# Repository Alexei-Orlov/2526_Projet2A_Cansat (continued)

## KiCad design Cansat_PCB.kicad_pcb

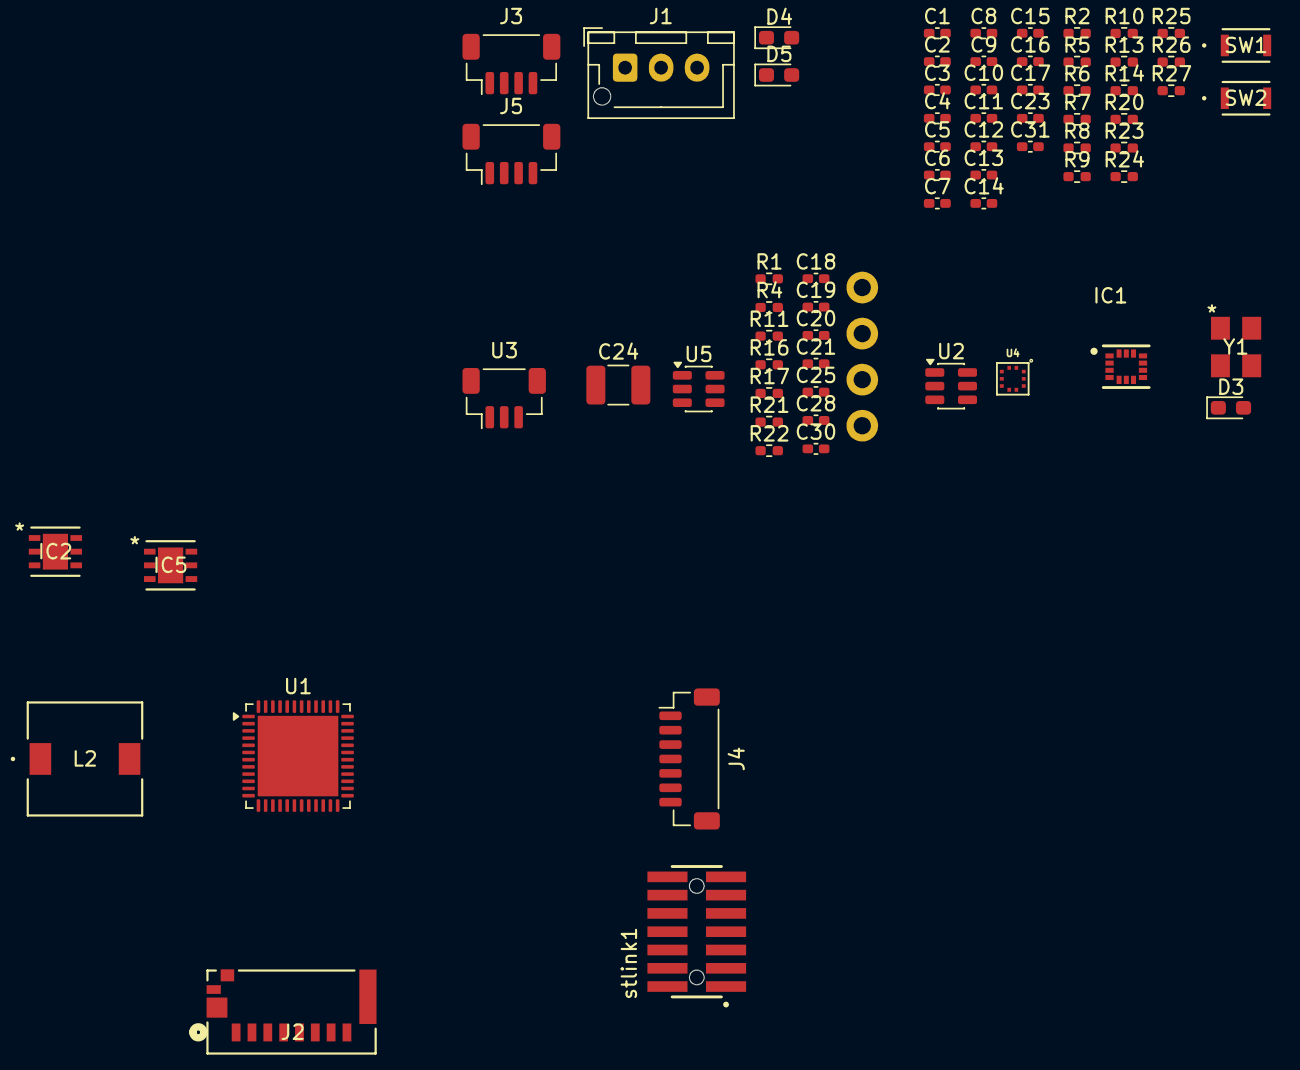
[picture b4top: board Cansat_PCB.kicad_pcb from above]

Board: 2 copper layers, 74 parts (0 on the bottom side), 50 nets, no tracks yet.

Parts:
C1, C4, C5, C6, C9, C16, C23, C30, C31: 100n; C_0402_1005Metric_Pad0.74x0.62mm_HandSolder
C2: 0.1u; C_0402_1005Metric_Pad0.74x0.62mm_HandSolder
C3, C7, C14: 10n; C_0402_1005Metric_Pad0.74x0.62mm_HandSolder
C8, C10, C18, C19, C20, C21: 1u; C_0402_1005Metric_Pad0.74x0.62mm_HandSolder
C11, C15: 4.7u; C_0402_1005Metric_Pad0.74x0.62mm_HandSolder
C12, C13: 16p; C_0402_1005Metric_Pad0.74x0.62mm_HandSolder
C17: 10u; C_0402_1005Metric_Pad0.74x0.62mm_HandSolder
C24: 0.1u; C_1210_3225Metric_Pad1.33x2.70mm_HandSolder
C25: 2.2u; C_0402_1005Metric_Pad0.74x0.62mm_HandSolder
C28: 66u; C_0402_1005Metric_Pad0.74x0.62mm_HandSolder
D3, D4, D5: LED; LED_0603_1608Metric_Pad1.05x0.95mm_HandSolder
H1, H2, H3, H4: MountingHole_Pad; mountinghole1.2mm
IC1: 2536030320001; WSEN-ISDS_2536030320001
IC2, IC5: LDO40LPU33RY; DFN6_3X3_STM
J1: battery connector; JST_XH_B3B-XH-AM_1x03_P2.50mm_Vertical
J2: 47309-2651; CONN12_47309-2651_MOL
J3: connecteur gps; JST_SH_BM04B-SRSS-TB_1x04-1MP_P1.00mm_Vertical
J4: Conn_01x07_Pin; JST_SH_BM07B-SRSS-TB_1x07-1MP_P1.00mm_Vertical
J5: Conn_01x04_Pin; JST_SH_BM04B-SRSS-TB_1x04-1MP_P1.00mm_Vertical
L2: 10u; IND_WE-PD-SMT_7332_WRE
R1: 100k; R_0402_1005Metric_Pad0.72x0.64mm_HandSolder
R2, R5, R6, R22, R23, R25: 10k; R_0402_1005Metric_Pad0.72x0.64mm_HandSolder
R4, R11: 1k; R_0402_1005Metric_Pad0.72x0.64mm_HandSolder
R7, R8, R9, R10: 47k; R_0402_1005Metric_Pad0.72x0.64mm_HandSolder
R13, R14: 10R; R_0402_1005Metric_Pad0.72x0.64mm_HandSolder
R16: 53.6k; R_0402_1005Metric_Pad0.72x0.64mm_HandSolder
R17: 10.2k; R_0402_1005Metric_Pad0.72x0.64mm_HandSolder
R20: 1.1k; R_0402_1005Metric_Pad0.72x0.64mm_HandSolder
R21: 20k; R_0402_1005Metric_Pad0.72x0.64mm_HandSolder
R24: 0R; R_0402_1005Metric_Pad0.72x0.64mm_HandSolder
R26, R27: 2.2k; R_0402_1005Metric_Pad0.72x0.64mm_HandSolder
SW1: RSTBTN; KXT 321 LHS_CNK
SW2: boot; KXT 321 LHS_CNK
U1: STM32G431CBUx; QFN-48-1EP_7x7mm_P0.5mm_EP5.6x5.6mm
U2: USBLC6-2SC6; SOT-23-6
U3: Connecteur moteur; JST_SH_BM03B-SRSS-TB_1x03-1MP_P1.00mm_Vertical
U4: BMP581
U5: LMR51625; SOT-23-6
Y1: Crystal_GND24_Small; SMD3225_3.2X2.5X0.7_MTC
stlink1: FTSH-107-01-L-DV-K-A; SAMTEC_FTSH-107-01-L-DV-K-A

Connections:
3.3VEN: C20.1, C21.1, D4.2 (A), D5.2 (A), IC2.4 (VOUT), IC2.5 (VSENSE), IC5.4 (VOUT), IC5.5 (VSENSE), J3.1
+3.3V: C1.1, C4.2, C5.2, C6.2, C7.2, C8.2, C9.2, C10.2, C11.1, C15.1, C16.1, C17.1, IC1.2 (RSVD_1), IC1.3 (RSVD_2), IC1.5 (VDD_IO), IC1.8 (VDD), IC1.11 (RSVD_4), IC1.12 (CS), J2.4, J4.2, R5.1, R7.2, R8.1, R9.1, R10.2, R13.1, R14.1, R23.1, R25.2, R26.2, R27.1, SW2.2, U1.1 (VBAT), U1.20 (VREF+), U1.21 (VDDA), U1.23 (VDD), U1.35 (VDD), U1.48 (VDD), stlink1.03
+5V: C18.1, C19.1, C28.1, IC2.2 (EN), IC2.3 (VIN), IC5.3 (VIN), J5.1, L2.2, R16.2, U2.5 (VBUS), U3.2
ADC1_IN3_VBAT: C30.2, R21.1, R22.2, U1.10 (PA2)
BAROEXTI: R24.2, U1.12 (PA4)
D+: U1.34 (PA12), U2.4 (I/O2)
D-: U1.33 (PA11), U2.6 (I/O1)
DIO0_LoRa: J4.7, U1.42 (PB4)
GND: C1.2, C2.1, C3.1, C4.1, C5.1, C6.1, C7.1, C8.1, C9.1, C10.1, C11.2, C12.2, C13.1, C14.2, C15.2, C16.2, C17.2, C18.2, C19.2, C20.2, C21.2, C23.2, C25.2, C28.2, C30.1, C31.2, H1.1, H2.1, H3.1, H4.1, IC1.6 (GND_1), IC1.7 (GND_2), IC2.1 (GND), IC2.7 (EPAD), IC5.1 (GND), IC5.7 (EP), J1.1, J2.6, J2.G1, J2.G2, J2.G4, J3.4, J4.1, J5.4, R1.2, R2.2, R4.1, R11.1, R17.2, R20.1, R22.1, SW1.1, U1.49 (VSS), U2.2 (GND), U3.1, U3.MP, U4.3 (VSS_1), U4.8 (VSS_2), U4.9 (VSS_3), U5.1 (GND), Y1.2, Y1.4, stlink1.05, stlink1.07, stlink1.11
I2C1_SCL: R27.2, U1.38 (PA15), U4.2 (SCK)
I2C1_SDA: R26.1, U1.47 (PB9), U4.4 (SDI)
I2C3_SCL_ACCEL: IC1.13 (SCL), R9.2, U1.30 (PA8)
I2C3_SDA_ACCEL: IC1.14 (SDA), R10.1, U1.40 (PC11)
NRST: C2.2, SW1.2, U1.7 (PG10), stlink1.12
unnamed: D3.2 (A), U1.17 (PB0)
unnamed: D3.1 (K), R20.2
unnamed: D4.1 (K), R4.2
unnamed: D5.1 (K), R11.2
unnamed: J2.G3, R5.2, R6.1
unnamed: C13.2, U1.5 (PF0), Y1.1
unnamed: C12.1, U1.6 (PF1), Y1.3
unnamed: R23.2, U4.6 (CSB)
unnamed: R24.1, U4.7 (INT)
unnamed: R25.1, U4.5 (SDO)
unnamed: C23.1, R14.2, U4.10 (VDD)
unnamed: C31.1, R13.2, U4.1 (VDDIO)
unnamed: C24.1, U5.6 (CB)
unnamed: R16.1, R17.1, U5.4 (FB)
unnamed: C24.2, L2.1, U5.2 (SW)
PWEN: IC5.2 (EN), R1.1, U1.43 (PB5)
SDDETECT: C14.1, R6.2, U1.19 (PB2)
SPI1_CS_SD: J2.2, U1.16 (PC4)
SPI1_MISO_SD: J2.7, R8.2, U1.14 (PA6)
SPI1_MOSI_SD: J2.3, R7.1, U1.15 (PA7)
SPI1_SCK_SD: J2.5, U1.13 (PA5)
SPI2_MISO_LoRa: J4.5, U1.27 (PB14)
SPI2_MOSI_LoRa: J4.4, U1.28 (PB15)
SPI2_NSS/CS: J4.6, U1.25 (PB12)
SPI2_SCK_LoRa: J4.3, U1.26 (PB13)
SWCLK/I2C1_SDA: U1.37 (PA14), stlink1.06
SWDIO: U1.36 (PA13), stlink1.04
TIM3_CHI_PWM4: U1.29 (PC6), U3.3
USART1_RX_GPS: J3.2, U1.45 (PB7)
USART1_STLINK_RX: U1.32 (PA10), stlink1.13
USART1_STLINK_TX: U1.31 (PA9), stlink1.14
USART1_TX_GPS: J3.3, U1.44 (PB6)
USART3_RX: C3.2, R2.1, SW2.1, U1.46 (PB8)
USART_TOF_RX: J5.2, U1.24 (PB11)
USART_TOF_TX: J5.3, U1.39 (PC10)
VIN: C25.1, J1.3, R21.2, U5.3 (VIN), U5.5 (EN)

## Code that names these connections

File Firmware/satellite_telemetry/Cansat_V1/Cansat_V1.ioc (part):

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Mcu.Name=STM32G431C(6-8-B)Ux
Mcu.Package=UFQFPN48
Mcu.UserName=STM32G431CBUx
PA13.Mode=Serial_Wire
PA13.Signal=SYS_JTMS-SWDIO
PA14.Mode=Serial_Wire
PA14.Signal=SYS_JTCK-SWCLK
PA15.GPIOParameters=GPIO_Speed,GPIO_Label,GPIO_Pu
PA15.GPIO_Label=BARO_I2C1_SCL
PA15.GPIO_Pu=GPIO_PULLUP
PA15.GPIO_Speed=GPIO_SPEED_FREQ_VERY_HIGH
PA15.Mode=I2C
PA15.Signal=I2C1_SCL
PA2.GPIOParameters=GPIO_Label
PA2.GPIO_Label=VBAT_ADC1_IN3
PA2.Mode=IN3-Single-Ended
PA2.Signal=ADC1_IN3
PA3.GPIOParameters=GPIO_PuPd,GPIO_Label,GPIO_ModeDefaultEXTI
PA3.GPIO_Label=HMIBTN_EXTI3
PA3.GPIO_ModeDefaultEXTI=GPIO_MODE_IT_RISING_FALLING
PA3.GPIO_PuPd=GPIO_PULLDOWN
PA3.Signal=GPXTI3
PA5.GPIOParameters=GPIO_Label
PA5.GPIO_Label=SD_SPI1_SCK
PA5.Mode=Full_Duplex_Master
PA5.Signal=SPI1_SCK
PA6.GPIOParameters=GPIO_Label
PA6.GPIO_Label=SD_SPI1_MISO
PA6.Mode=Full_Duplex_Master
PA6.Signal=SPI1_MISO
PA7.GPIOParameters=GPIO_Label
PA7.GPIO_Label=SD_SPI1_MOSI
PA7.Mode=Full_Duplex_Master
PA7.Signal=SPI1_MOSI
PA8.GPIOParameters=GPIO_Label
PA8.GPIO_Label=IMU_I2C3_SCL
PA8.Mode=I2C
PA8.Signal=I2C3_SCL
PB0.GPIOParameters=GPIO_Label
PB0.GPIO_Label=LED_GPIO_OUT
PB0.Signal=GPIO_Output
PB10.GPIOParameters=GPIO_Label
PB10.GPIO_Label=HMILED_GPIO
PB10.Signal=GPIO_Output
PB11.GPIOParameters=GPIO_Label
PB11.GPIO_Label=LIDAR_USART3_RX
PB11.Mode=Asynchronous
PB11.Signal=USART3_RX
PB12.GPIOParameters=GPIO_Label
PB12.GPIO_Label=LORA_NSS
PB12.Signal=GPIO_Output
PB13.GPIOParameters=GPIO_Speed,GPIO_PuPd,GPIO_Label,GPIO_Mode
PB13.GPIO_Label=LORA_SPI2_SCK
PB13.GPIO_Mode=GPIO_MODE_AF_PP
PB13.GPIO_PuPd=GPIO_NOPULL
PB13.GPIO_Speed=GPIO_SPEED_FREQ_LOW
PB13.Mode=Full_Duplex_Master
PB13.Signal=SPI2_SCK
PB14.GPIOParameters=GPIO_Speed,GPIO_PuPd,GPIO_Label,GPIO_Mode
PB14.GPIO_Label=LORA_SPI2_MISO
PB14.GPIO_Mode=GPIO_MODE_AF_PP
PB14.GPIO_PuPd=GPIO_NOPULL
PB14.GPIO_Speed=GPIO_SPEED_FREQ_LOW
PB14.Mode=Full_Duplex_Master
PB14.Signal=SPI2_MISO
PB15.GPIOParameters=GPIO_Speed,GPIO_PuPd,GPIO_Label,GPIO_Mode
PB15.GPIO_Label=LORA_SPI2_MOSI
PB15.GPIO_Mode=GPIO_MODE_AF_PP
PB15.GPIO_PuPd=GPIO_NOPULL
PB15.GPIO_Speed=GPIO_SPEED_FREQ_LOW
PB15.Mode=Full_Duplex_Master
PB15.Signal=SPI2_MOSI
PB2.GPIOParameters=GPIO_Label
PB2.GPIO_Label=SD_GPIO_DETECT
PB2.Signal=GPIO_Input
PB3.Signal=SYS_JTDO-SWO
PB4.GPIOParameters=GPIO_Label
PB4.GPIO_Label=LORA_RST
PB4.Signal=GPIO_Output
PB5.GPIOParameters=GPIO_Label
PB5.GPIO_Label=VPOWER_EN_GPIO_OUT
PB5.Signal=GPIO_Output
PB6.GPIOParameters=GPIO_Speed,GPIO_Label
PB6.GPIO_Label=STLINK_GPS_USART1-TX
PB6.GPIO_Speed=GPIO_SPEED_FREQ_HIGH
PB6.Mode=Asynchronous
PB6.Signal=USART1_TX
PB7.GPIOParameters=GPIO_Speed,GPIO_Label
PB7.GPIO_Label=STLINK_GPS_USART1-RX
PB7.GPIO_Speed=GPIO_SPEED_FREQ_HIGH
PB7.Mode=Asynchronous
PB7.Signal=USART1_RX
PB9.GPIOParameters=GPIO_Speed,GPIO_Label,GPIO_Pu
PB9.GPIO_Label=BARO_I2C1_SDA
PB9.GPIO_Pu=GPIO_PULLUP
PB9.GPIO_Speed=GPIO_SPEED_FREQ_VERY_HIGH
PB9.Mode=I2C
PB9.Signal=I2C1_SDA
PC10.GPIOParameters=GPIO_Label
PC10.GPIO_Label=LIDAR_USART3_TX
PC10.Mode=Asynchronous
PC10.Signal=USART3_TX
PC11.GPIOParameters=GPIO_Label
PC11.GPIO_Label=IMU_I2C3_SDA
PC11.Mode=I2C
PC11.Signal=I2C3_SDA
PC4.GPIOParameters=GPIO_Label
PC4.GPIO_Label=SD_GPIO_CS
PC4.Signal=GPIO_Output
PC6.GPIOParameters=GPIO_Label
PC6.GPIO_Label=MOTOR_TIM3_CH1
PC6.Signal=S_TIM3_CH1
PF0-OSC_IN.Mode=HSE-External-Oscillator
PF0-OSC_IN.Signal=RCC_OSC_IN
PF1-OSC_OUT.Mode=HSE-External-Oscillator
PF1-OSC_OUT.Signal=RCC_OSC_OUT
RCC.HSE_VALUE=12000000
RCC.SYSCLKFreq_VALUE=170000000
RCC.SYSCLKSource=RCC_SYSCLKSOURCE_PLLCLK
board=custom

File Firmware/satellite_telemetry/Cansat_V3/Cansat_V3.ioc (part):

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Mcu.Name=STM32G431C(6-8-B)Ux
Mcu.Package=UFQFPN48
Mcu.UserName=STM32G431CBUx
PA13.Mode=Serial_Wire
PA13.Signal=SYS_JTMS-SWDIO
PA14.Mode=Serial_Wire
PA14.Signal=SYS_JTCK-SWCLK
PA15.GPIOParameters=GPIO_Speed,GPIO_Label,GPIO_Pu
PA15.GPIO_Label=BARO_I2C1_SCL
PA15.GPIO_Pu=GPIO_PULLUP
PA15.GPIO_Speed=GPIO_SPEED_FREQ_VERY_HIGH
PA15.Mode=I2C
PA15.Signal=I2C1_SCL
PA5.GPIOParameters=GPIO_Label
PA5.GPIO_Label=SD_SPI1_SCK
PA5.Mode=Full_Duplex_Master
PA5.Signal=SPI1_SCK
PA6.GPIOParameters=GPIO_Label
PA6.GPIO_Label=SD_SPI1_MISO
PA6.Mode=Full_Duplex_Master
PA6.Signal=SPI1_MISO
PA7.GPIOParameters=GPIO_Label
PA7.GPIO_Label=SD_SPI1_MOSI
PA7.Mode=Full_Duplex_Master
PA7.Signal=SPI1_MOSI
PA8.GPIOParameters=GPIO_Label
PA8.GPIO_Label=IMU_I2C3_SCL
PA8.Mode=I2C
PA8.Signal=I2C3_SCL
PB0.GPIOParameters=GPIO_Label
PB0.GPIO_Label=LED_GPIO_OUT
PB0.Signal=GPIO_Output
PB1.GPIOParameters=GPIO_Label
PB1.GPIO_Label=VBAT_ADC1_IN12
PB1.Mode=IN12-Single-Ended
PB1.Signal=ADC1_IN12
PB10.GPIOParameters=GPIO_Label
PB10.GPIO_Label=HMILED_GPIO
PB10.Signal=GPIO_Output
PB11.GPIOParameters=GPIO_Label
PB11.GPIO_Label=LIDAR_USART3_RX
PB11.Mode=Asynchronous
PB11.Signal=USART3_RX
PB12.GPIOParameters=GPIO_Label
PB12.GPIO_Label=LORA_NSS
PB12.Signal=GPIO_Output
PB13.GPIOParameters=GPIO_Speed,GPIO_PuPd,GPIO_Label,GPIO_Mode
PB13.GPIO_Label=LORA_SPI2_SCK
PB13.GPIO_Mode=GPIO_MODE_AF_PP
PB13.GPIO_PuPd=GPIO_NOPULL
PB13.GPIO_Speed=GPIO_SPEED_FREQ_LOW
PB13.Mode=Full_Duplex_Master
PB13.Signal=SPI2_SCK
PB14.GPIOParameters=GPIO_Speed,GPIO_PuPd,GPIO_Label,GPIO_Mode
PB14.GPIO_Label=LORA_SPI2_MISO
PB14.GPIO_Mode=GPIO_MODE_AF_PP
PB14.GPIO_PuPd=GPIO_NOPULL
PB14.GPIO_Speed=GPIO_SPEED_FREQ_LOW
PB14.Mode=Full_Duplex_Master
PB14.Signal=SPI2_MISO
PB15.GPIOParameters=GPIO_Speed,GPIO_PuPd,GPIO_Label,GPIO_Mode
PB15.GPIO_Label=LORA_SPI2_MOSI
PB15.GPIO_Mode=GPIO_MODE_AF_PP
PB15.GPIO_PuPd=GPIO_NOPULL
PB15.GPIO_Speed=GPIO_SPEED_FREQ_LOW
PB15.Mode=Full_Duplex_Master
PB15.Signal=SPI2_MOSI
PB2.GPIOParameters=GPIO_Label
PB2.GPIO_Label=SD_GPIO_DETECT
PB2.Signal=GPIO_Input
PB3.Signal=SYS_JTDO-SWO
PB4.GPIOParameters=GPIO_Label
PB4.GPIO_Label=LORA_RST
PB4.Signal=GPIO_Output
PB5.GPIOParameters=GPIO_Label
PB5.GPIO_Label=VPOWER_EN_GPIO_OUT
PB5.Signal=GPIO_Output
PB6.GPIOParameters=GPIO_Speed,GPIO_Label
PB6.GPIO_Label=STLINK_GPS_USART1-TX
PB6.GPIO_Speed=GPIO_SPEED_FREQ_HIGH
PB6.Mode=Asynchronous
PB6.Signal=USART1_TX
PB7.GPIOParameters=GPIO_Speed,GPIO_Label
PB7.GPIO_Label=STLINK_GPS_USART1-RX
PB7.GPIO_Speed=GPIO_SPEED_FREQ_HIGH
PB7.Mode=Asynchronous
PB7.Signal=USART1_RX
PB9.GPIOParameters=GPIO_Speed,GPIO_Label,GPIO_Pu
PB9.GPIO_Label=BARO_I2C1_SDA
PB9.GPIO_Pu=GPIO_PULLUP
PB9.GPIO_Speed=GPIO_SPEED_FREQ_VERY_HIGH
PB9.Mode=I2C
PB9.Signal=I2C1_SDA
PC10.GPIOParameters=GPIO_Label
PC10.GPIO_Label=LIDAR_USART3_TX
PC10.Mode=Asynchronous
PC10.Signal=USART3_TX
PC11.GPIOParameters=GPIO_Label
PC11.GPIO_Label=IMU_I2C3_SDA
PC11.Mode=I2C
PC11.Signal=I2C3_SDA
PC13.GPIOParameters=GPIO_PuPd,GPIO_Label,GPIO_ModeDefaultEXTI
PC13.GPIO_Label=HMIBTN_EXTI13
PC13.GPIO_ModeDefaultEXTI=GPIO_MODE_IT_RISING_FALLING
PC13.GPIO_PuPd=GPIO_PULLDOWN
PC13.Signal=GPXTI13
PC4.GPIOParameters=GPIO_Label
PC4.GPIO_Label=SD_GPIO_CS
PC4.Signal=GPIO_Output
PC6.GPIOParameters=GPIO_Label
PC6.GPIO_Label=MOTOR_TIM3_CH1
PC6.Signal=S_TIM3_CH1
PF0-OSC_IN.Mode=HSE-External-Oscillator
PF0-OSC_IN.Signal=RCC_OSC_IN
PF1-OSC_OUT.Mode=HSE-External-Oscillator
PF1-OSC_OUT.Signal=RCC_OSC_OUT
RCC.HSE_VALUE=12000000
RCC.SYSCLKFreq_VALUE=170000000
RCC.SYSCLKSource=RCC_SYSCLKSOURCE_PLLCLK
board=custom

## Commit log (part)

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2025-09-14 Update README.md
    First Session log
    /!\ roles have to be clearly defined during next session
2025-09-23 Update README.md
    update for the session 15/09 the sessions still have to be moved to another file
2025-09-23 Create Notes
    to write things before we forget
2025-09-23 Create Links
2025-10-18 Moved the session logs from the Readme to logs.md
2025-10-21 Session logs only comms
    Updated October 21st
2025-10-24 Schematic du premier PCB
2025-10-25 Update README.md
    Removed the session logs, find it in logs.md
2025-10-25 Update logs.md
    moved the session logs in here
2025-10-25 Update README.md
    Strategy update : explanations of the current rules and added link to the Onshape folder
2025-10-25 Update README.md
    fixed some visual issues and added more links to documentations
2025-10-26 Schematic upgrade WARNING : there ar still issues to be solved before routing and the accelerometer should be changed to the BNO055
2025-10-26 added BNO055 library
2025-10-29 Remplacement de l'accéléromètre par le BNO055 débuggage et modification des bibliothèques pou ne plus avoir de wanings lors de l'implémzbtation sur le PCB il faut cependant ajouter une led commandabl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
2025-11-02 ajout 2 Led adr + btn cmd + buck LMR51625 => sch complet sans warnings et erreurs
2025-11-03 routage non fini : ceci est un commit de transfert de fichier vers un autre PC
2025-11-10 nouvelles règles de routage Attention les pistes sont à l'ancienne taille : a corriger
2025-11-22 Update README.md
    updated mission descriptions
2025-11-22 Organisation des 6 couches + Placement des différents composants avant routage
2025-11-23 Début du routage
2025-11-24 Routage front , faire attention au VAROEXTI, Led Status et EXTI, back routgae a vérifier, certains composants semblent trop grands checker empreintes
2025-12-15 PCB_V1 added to main branch it is not a merge because the branch had encountered some issues and it required fixing without a git history
2025-12-16 Schématique + routage du PCB IHM
2025-12-18 Export des fichiers gerbers
2026-01-13 created images folder
2026-01-13 Added schematic images to the IMG folder
2026-01-13 Changed the name of the images
2026-01-13 changed the name of 2 images
2026-01-15 added reports folder
2026-01-16 readmeupdate
2026-01-16 Readme update and attempt to fix the 3d models
2026-01-16 Redame gif size issue fixed
2026-01-16 readme fix (again sorry)
2026-01-16 Readme addition : Kirigami diagram
2026-01-17 Document topography and data processing details
    Added section on topography and data processing for landing field measurements.
2026-01-22 Correction Alim LoRa/GPS, empreinte Buck LMR, ajout du connecteur IHM dans le schématique
2026-01-22 ajout du connecteur IHM dans l'éditeur de PCB
2026-01-23 addition of the presentation for the 1st year students
2026-02-03 Conn Camera 2 pins et deplacement du transistor dans un pcb intermédiaire
2026-02-03 schematic + routage pcb camera
2026-02-05 updated logs
2026-02-07 Fixing the 3D models issues
2026-02-09 finalisation de la mainboard
2026-02-10 vérification LED
2026-02-10 ajout du logo vortex
2026-02-20 Logo update plus trace arragments
2026-03-23 created Archives folder
2026-04-13 PCB_V2 added (not a merge to avoid conflicts)
2026-04-13 PCB_V3 added (not a merge to avoid conflicts)
2026-04-13 importing new readme
2026-04-13 small readme update with added documents
2026-04-13 added FSM image
2026-04-14 added the UART2 for the camera as well as M2 holes
2026-04-14 added marking to the testpoints
2026-04-15 Firmware readme update and Images rezising
2026-04-15 Add Button_Screen2 image to README
    Added a new image for the button pushed state in the README.
2026-04-15 Fix wording and clarify HMI PCB testing details
2026-04-15 Fix grammatical error in parachute dimensions section
2026-04-21 mega big readme update for the mechanical and wind tunnel parts
2026-04-21 onshape link fix
2026-04-22 updated readme and uploaded firmware section
2026-05-13 added GUI
2026-05-15 SD Card Working, implementation of the Lidar in progress
2026-05-15 using same format as station sol for the csv filesBattery task updates
2026-05-28 code update with lidar.csv, IHM
2026-05-28 fixed LIDAR.csv issues
2026-05-28 added lidar condition
2026-05-28 added formatting and recalib through hmi
2026-05-29 starting implementation of the new code : known issue freeze after a few seconds we suspect a memory overflow
2026-05-30 finally solved the bug that breaks the lidar when the power is turned off and on, as well as some fixes for the new formating ability
2026-06-13 added Baro EXTI and reduced LIDAR-IMU shift
2026-06-13 update with working exti for the barometer
2026-06-17 small bug fix with the calibration baro when power gets cut off
2026-06-19 fixed priority issue now the imu is at 100Hz but we have a baro issue
2026-06-21 working lora and SD card with XYZ accel
2026-06-24 backup just to be sure
